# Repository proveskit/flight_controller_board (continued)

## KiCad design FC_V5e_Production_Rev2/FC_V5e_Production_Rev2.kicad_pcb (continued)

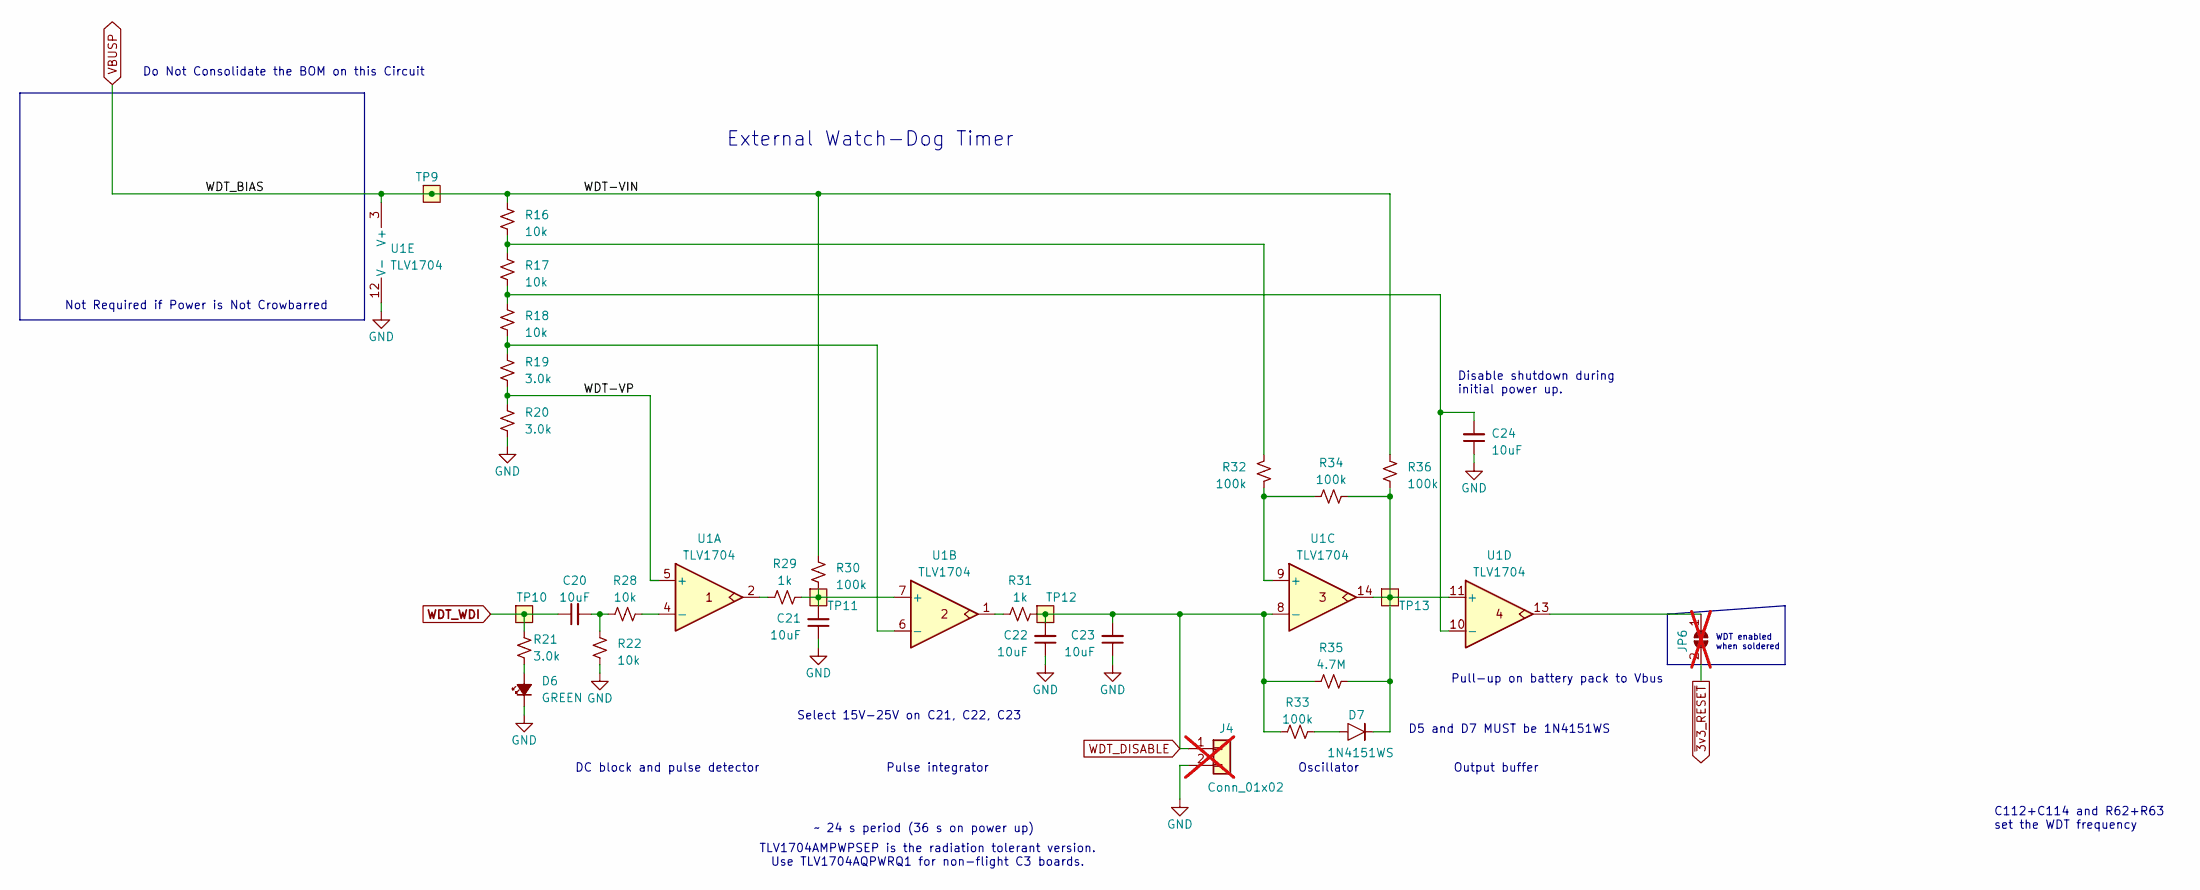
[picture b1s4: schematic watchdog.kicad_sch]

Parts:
C20, C24: 10uF; C_0603_1608Metric; MPN GRT188R61C106KE13D
C21, C22, C23: 10uF; C_0603_1608Metric; MPN CL10A106MA8NRNC
D6: GREEN; LED_0603_1608Metric; MPN 150060GS75000
D7: 1N4151WS; D_SOD-323; MPN 1N4151WS-E3-08
J4: Conn_01x02; PinHeader_1x02_P2.54mm_Vertical; not fitted
JP6: SolderJumper_2_Open; SolderJumper-2_P1.3mm_Open_RoundedPad1.0x1.5mm; not fitted
R16, R17, R18, R22, R28: 10k; R_0603_1608Metric; MPN RMCF0603FT10K0
R19, R20, R21: 3.0k; R_0603_1608Metric; MPN RMCF0603FT3K00
R29, R31: 1k; R_0603_1608Metric; MPN RMCF0603FT1K00
R30, R32, R33, R34, R36: 100k; R_0603_1608Metric; MPN RMCF0603FT100K
R35: 4.7M; R_0603_1608Metric; MPN RMCF0603FT4M70
TP9, TP10, TP11, TP12, TP13: TestPoint-MinTH; TestPoint-0.75mm-th
U1: TLV1704; TSSOP-14_4.4x5mm_P0.65mm; MPN TLV1704AQPWRQ1

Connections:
/Watchdog Circuit/WDT-VP: R19.2, R20.1, U1.5 (+)
GND: C21.1, C22.1, C23.1, C24.1, D6.1 (K), J4.2, R20.2, R22.2, U1.12 (V-); also elsewhere on the board
unnamed: C20.2, R22.1, R28.1
unnamed: D6.2 (A), R21.2
unnamed: D7.2, R33.1
unnamed: JP6.1 (A), U1.13
unnamed: R16.2, R17.1, R32.2
unnamed: R29.1, U1.2
unnamed: R31.1, U1.1
unnamed: R28.2, U1.4 (-)
unnamed: C21.2, R29.2, R30.2, TP11.1, U1.7 (+)
unnamed: R18.2, R19.1, U1.6 (-)
unnamed: R32.1, R34.1, U1.9 (+)
unnamed: D7.1, R34.2, R35.1, R36.1, TP13.1, U1.11 (+), U1.14
unnamed: C24.2, R17.2, R18.1, U1.10 (-)
VBUSP: R16.1, R30.1, R36.2, TP9.1, U1.3 (V+); also elsewhere on the board
WDT_DISABLE: C22.2, C23.2, J4.1, R31.2, R33.2, R35.2, TP12.1, U1.8 (-); also elsewhere on the board
WDT_WDI: C20.1, R21.1, TP10.1; also elsewhere on the board
~3v3_RESET: JP6.2 (B); also elsewhere on the board

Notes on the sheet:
Pull-up on battery pack to Vbus
Do Not Consolidate the BOM on this Circuit
Pulse integrator
Disable shutdown during initial power up.
~ 24 s period (36 s on power up)
D5 and D7 MUST be 1N4151WS
C112+C114 and R62+R63 set the WDT frequency
TLV1704AMPWPSEP is the radiation tolerant version. Use TLV1704AQPWRQ1 for non-flight C3 boards.
Select 15V-25V on C21, C22, C23
DC block and pulse detector
Oscillator
Output buffer
WDT enabled when soldered
External Watch-Dog Timer
Not Required if Power is Not Crowbarred

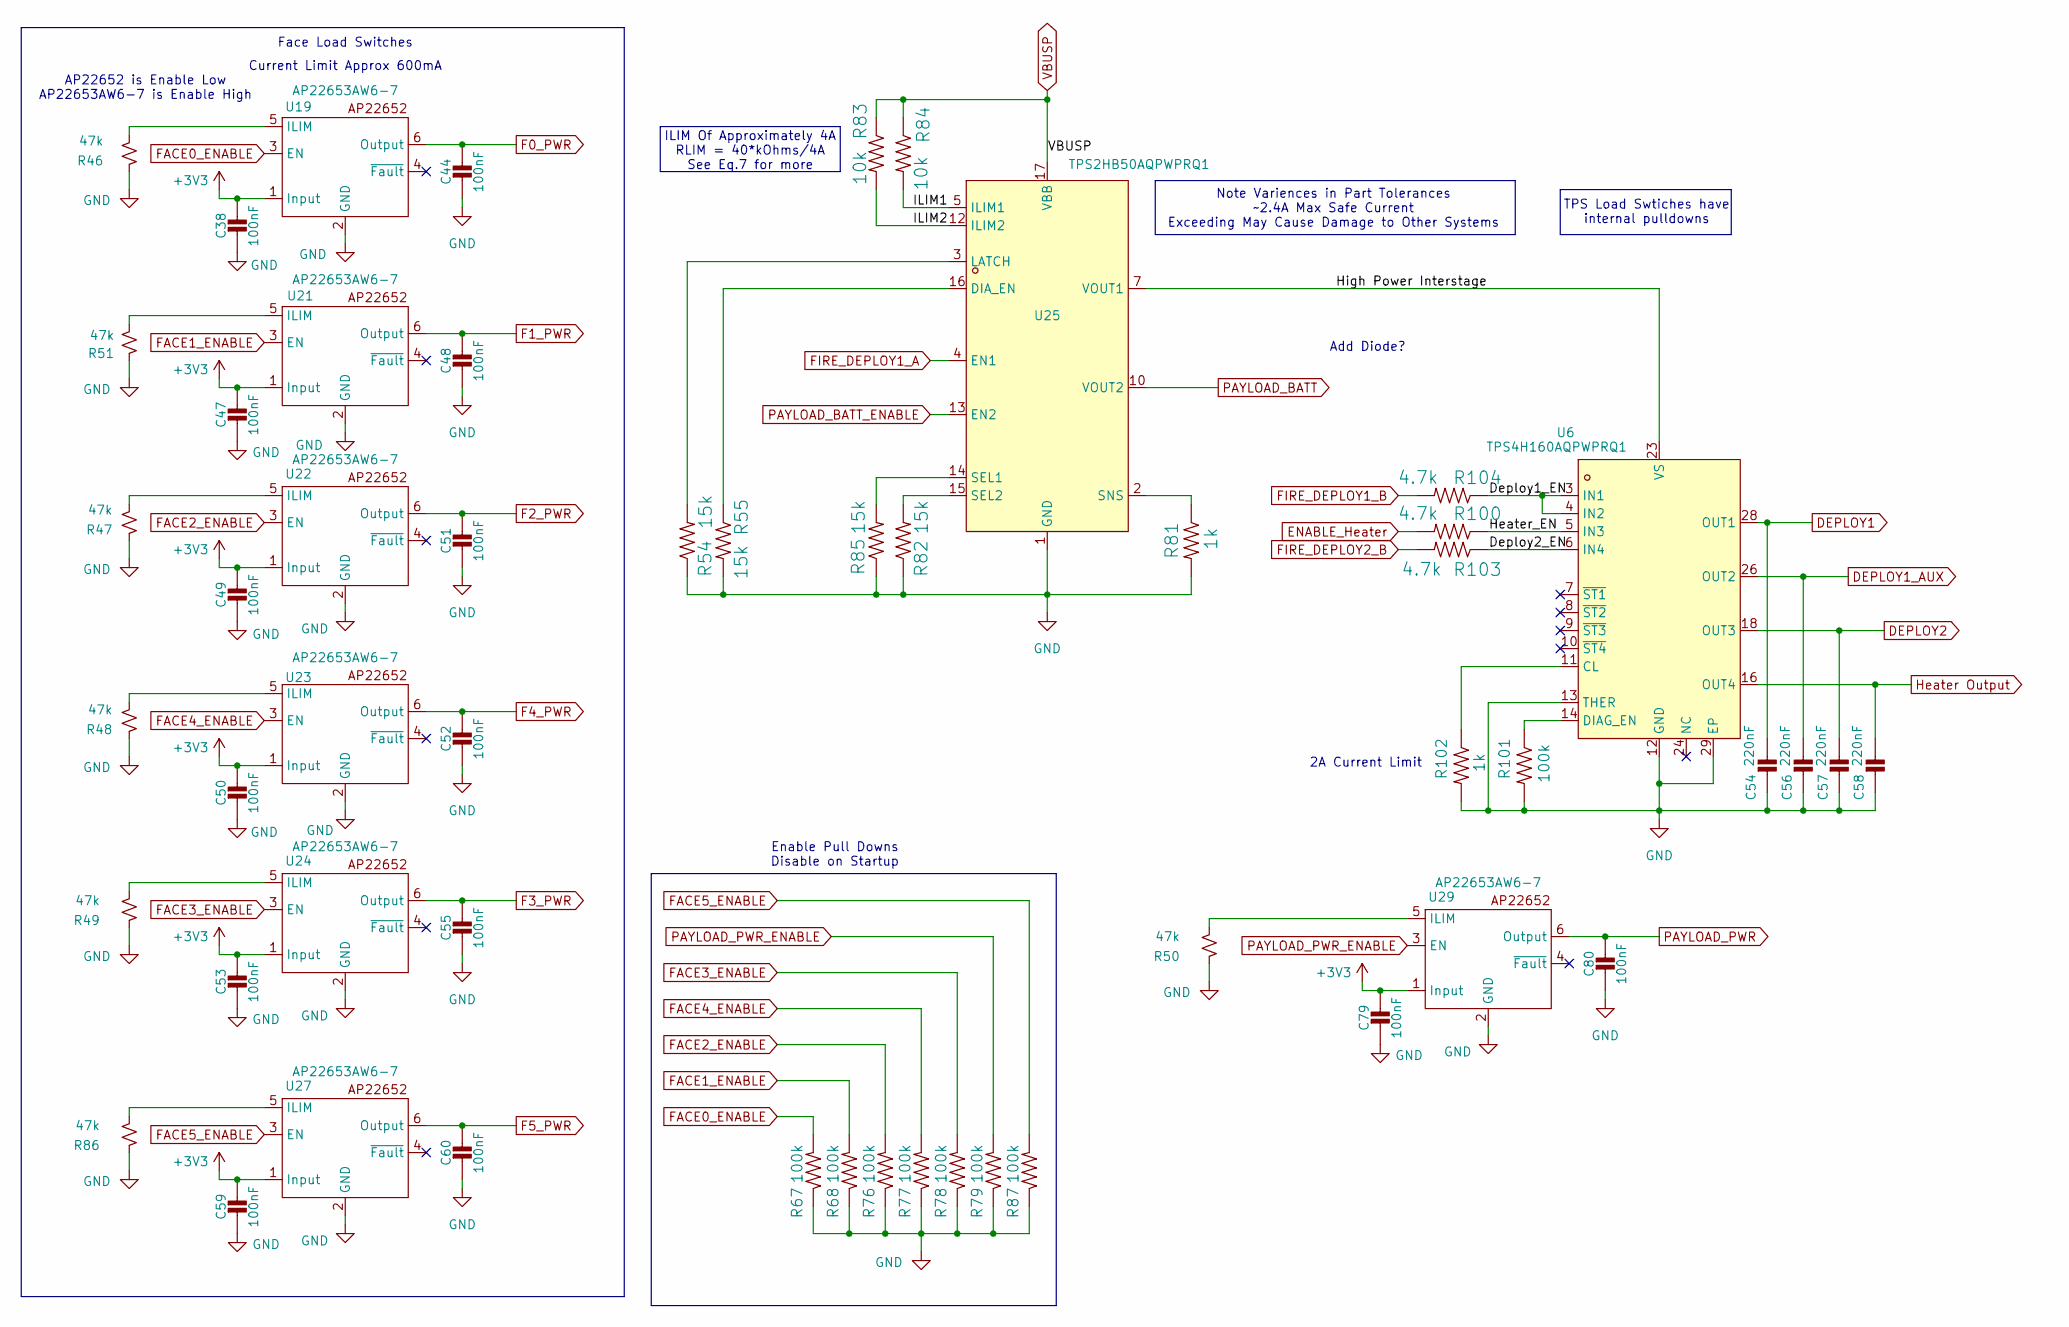
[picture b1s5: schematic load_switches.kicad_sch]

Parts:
C38, C44, C47, C48, C49, C50, C51, C52, C53, C55, C59, C60, C79, C80: 100nF; C_0402_1005Metric
C54, C56, C57, C58: 220nF; C_0402_1005Metric
R46, R47, R48, R49, R50, R51, R86: 47k; R_0603_1608Metric; MPN RMCF0603FT47K0
R54, R55, R82, R85: 15k; R_0603_1608Metric
R67, R68, R76, R77, R78, R79, R87, R101: 100k; R_0603_1608Metric
R81, R102: 1k; R_0603_1608Metric
R83, R84: 10k; R_0603_1608Metric
R100, R103, R104: 4.7k; R_0402_1005Metric
U6: TPS4H160AQPWPRQ1; HTSSOP-28_L9.7-W4.4-P0.65-LS6.4-BL-EP; LCSC Part C485918
U19, U21, U22, U23, U24, U27, U29: AP22653AW6-7; SOT26
U25: TPS2HB50AQPWPRQ1; HTSSOP-16_L5.0-W4.4-P0.65-LS6.4-BL-EP-2; LCSC Part C1857514

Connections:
+3V3: C38.1, C47.1, C49.1, C50.1, C53.1, C59.1, C79.1, U19.1 (Input), U21.1 (Input), U22.1 (Input), U23.1 (Input), U24.1 (Input), U27.1 (Input), U29.1 (Input); also elsewhere on the board
/Power Systems/Load Switches/Deploy1_EN: R104.1, U6.3 (IN1), U6.4 (IN2)
/Power Systems/Load Switches/Deploy2_EN: R103.1, U6.6 (IN4)
/Power Systems/Load Switches/Heater_EN: R100.1, U6.5 (IN3)
/Power Systems/Load Switches/High Power Interstage: U6.20 (VS), U6.21 (VS), U6.22 (VS), U6.23 (VS), U25.6 (VOUT1), U25.7 (VOUT1), U25.8 (VOUT1)
/Power Systems/Load Switches/ILIM1: R84.2, U25.5 (ILIM1)
/Power Systems/Load Switches/ILIM2: R83.2, U25.12 (ILIM2)
DEPLOY1: C54.1, U6.27 (OUT1), U6.28 (OUT1); also elsewhere on the board
DEPLOY1_AUX: C56.1, U6.25 (OUT2), U6.26 (OUT2); also elsewhere on the board
DEPLOY2: C57.1, U6.17 (OUT3), U6.18 (OUT3); also elsewhere on the board
ENABLE_Heater: R100.2; also elsewhere on the board
F0_PWR: C44.1, U19.6 (Output); also elsewhere on the board
F1_PWR: C48.1, U21.6 (Output); also elsewhere on the board
F2_PWR: C51.1, U22.6 (Output); also elsewhere on the board
F3_PWR: C55.1, U24.6 (Output); also elsewhere on the board
F4_PWR: C52.1, U23.6 (Output); also elsewhere on the board
F5_PWR: C60.1, U27.6 (Output); also elsewhere on the board
FACE0_ENABLE: R67.2, U19.3 (EN); also elsewhere on the board
FACE1_ENABLE: R68.2, U21.3 (EN); also elsewhere on the board
FACE2_ENABLE: R76.2, U22.3 (EN); also elsewhere on the board
FACE3_ENABLE: R78.2, U24.3 (EN); also elsewhere on the board
FACE4_ENABLE: R77.2, U23.3 (EN); also elsewhere on the board
FACE5_ENABLE: R87.2, U27.3 (EN); also elsewhere on the board
FIRE_DEPLOY1_A: U25.4 (EN1); also elsewhere on the board
FIRE_DEPLOY1_B: R104.2; also elsewhere on the board
FIRE_DEPLOY2_B: R103.2; also elsewhere on the board
GND: C38.2, C44.2, C47.2, C48.2, C49.2, C50.2, C51.2, C52.2, C53.2, C54.2, C55.2, C56.2, C57.2, C58.2, C59.2, C60.2, C79.2, C80.2, R46.1, R47.1, R48.1, R49.1, R50.1, R51.1, R54.1, R55.2, R67.1, R68.1, R76.1, R77.1, R78.1, R79.1, R81.2, R82.1, R85.1, R86.1, R87.1, R101.2, R102.2, U6.1 (GND), U6.12 (GND), U6.13 (THER), U6.29 (EP), U19.2 (GND), U21.2 (GND), U22.2 (GND), U23.2 (GND), U24.2 (GND), U25.1 (GND), U27.2 (GND), U29.2 (GND); also elsewhere on the board
Heater Output: C58.1, U6.15 (OUT4), U6.16 (OUT4); also elsewhere on the board
unnamed: R102.1, U6.11 (CL)
unnamed: R101.1, U6.14 (DIAG_EN)
unnamed: R46.2, U19.5 (ILIM)
unnamed: R51.2, U21.5 (ILIM)
unnamed: R47.2, U22.5 (ILIM)
unnamed: R48.2, U23.5 (ILIM)
unnamed: R49.2, U24.5 (ILIM)
unnamed: R55.1, U25.16 (DIA_EN)
unnamed: R54.2, U25.3 (LATCH)
unnamed: R85.2, U25.14 (SEL1)
unnamed: R82.2, U25.15 (SEL2)
unnamed: R81.1, U25.2 (SNS)
unnamed: R86.2, U27.5 (ILIM)
unnamed: R50.2, U29.5 (ILIM)
PAYLOAD_BATT: U25.9 (VOUT2), U25.10 (VOUT2), U25.11 (VOUT2); also elsewhere on the board
PAYLOAD_BATT_ENABLE: U25.13 (EN2); also elsewhere on the board
PAYLOAD_PWR: C80.1, U29.6 (Output); also elsewhere on the board
PAYLOAD_PWR_ENABLE: R79.2, U29.3 (EN); also elsewhere on the board
VBUSP: R83.1, R84.1, U25.17 (VBB); also elsewhere on the board

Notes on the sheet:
Current Limit Approx 600mA
ILIM Of Approximately 4A RLIM = 40*kOhms/4A See Eq.7 for more
TPS Load Swtiches have internal pulldowns
Add Diode?
Note Variences in Part Tolerances ~2.4A Max Safe Current Exceeding May Cause Damage to Other Systems
2A Current Limit
AP22652 is Enable Low AP22653AW6-7 is Enable High
Enable Pull Downs Disable on Startup
Face Load Switches

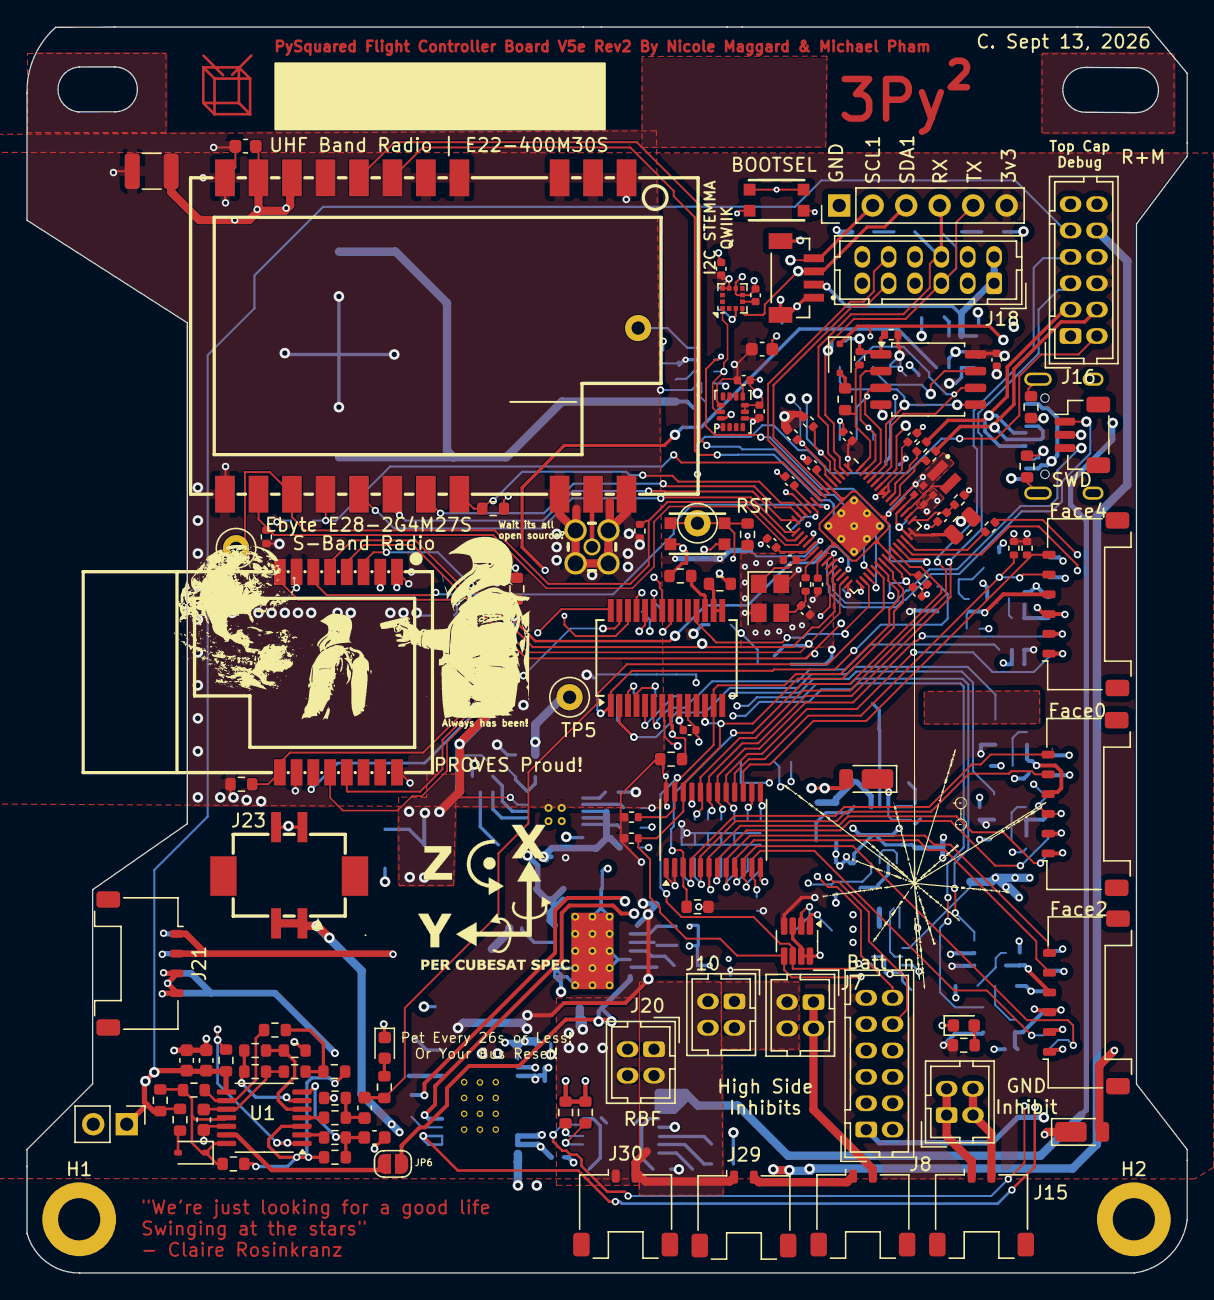
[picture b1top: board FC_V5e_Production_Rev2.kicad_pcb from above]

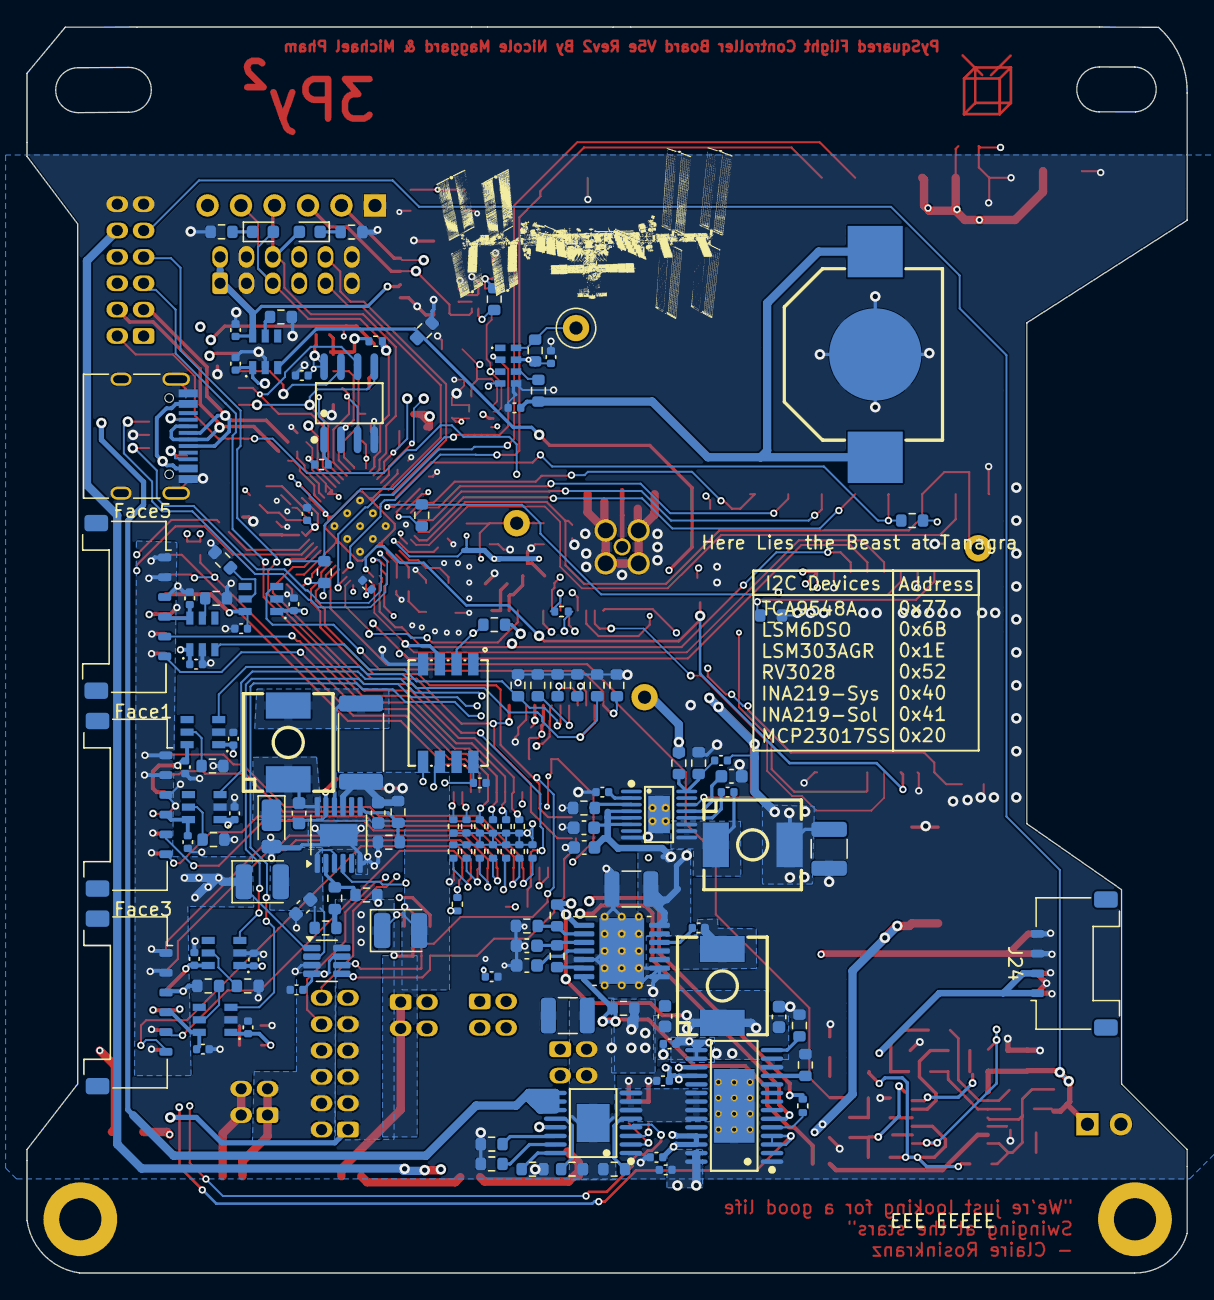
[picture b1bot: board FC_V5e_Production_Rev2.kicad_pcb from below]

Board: 4 copper layers, 88.0 x 94.5 mm, 256 parts (136 on the bottom side), 175 nets.

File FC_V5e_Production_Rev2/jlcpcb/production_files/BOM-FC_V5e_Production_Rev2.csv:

Comment,Designator,Footprint,LCSC,Quantity
0,R91,R_0402_1005Metric,C17168,1
0.1,R75,R_2512_6332Metric,C81248,1
100k,"R101,R30,R32,R33,R34,R36,R43,R65,R66,R67,R68,R76,R77,R78,R79,R80,R87,R92,R95,R96",R_0603_1608Metric,C25803,20
100nF,"C10,C18,C2,C26,C27,C28,C29,C30,C32,C34,C35,C38,C39,C44,C47,C48,C49,C5,C50,C51,C52,C53,C55,C59,C60,C67,C70,C71,C72,C73,C74,C76,C77,C78,C79,C80",C_0402_1005Metric,C1525,36
100uF,"C11,C19,C25",C_1210_3225Metric,C90143,3
10k,"R2,R37",R_0402_1005Metric,C25744,2
10k,"R1,R107,R11,R124,R13,R14,R15,R16,R17,R18,R22,R24,R28,R5,R52,R70,R83,R84,R90,R97",R_0603_1608Metric,C25804,20
10nF,C6,C_0402_1005Metric,C15195,1
10pF,C12,C_0402_1005Metric,C32949,1
10uF,C75,C_0805_2012Metric,C15850,1
10uF,"C1,C14,C20,C21,C22,C23,C24,C3,C40,C42,C43",C_0603_1608Metric,C19702,11
15k,"R54,R55,R82,R85",R_0603_1608Metric,C22809,4
15pF,"C63,C64",C_0402_1005Metric,C1548,2
1M,R63,R_0603_1608Metric,C22935,1
1N4151WS,D7,D_SOD-323,C17429783,1
1k,R93,R_0402_1005Metric,C11702,1
1k,"R10,R102,R29,R3,R31,R4,R64,R81",R_0603_1608Metric,C21190,8
1uF,"C37,C4,C41",C_0603_1608Metric,C15849,3
22,"R7,R8",R_0402_1005Metric,C25092,2
22.1k,R40,R_0603_1608Metric,C137768,1
220nF,"C31,C54,C56,C57,C58",C_0402_1005Metric,C16772,5
22uF,"C15,C16",C_0603_1608Metric,C59461,2
243k,R23,R_0603_1608Metric,C861248,1
2mOhm,"R108,R109",LED_1210_3225Metric,C92124,2
3.0k,"R19,R20,R21",R_0603_1608Metric,C4211,3
3.3nF,C36,C_0603_1608Metric,C1613,1
3.3u,L3,L_pol_2016,C42411119,1
33,R94,R_0402_1005Metric,C25105,1
4.7M,R35,R_0603_1608Metric,C18335,1
4.7k,"R100,R103,R104,R105,R106,R110,R111,R25,R39,R41,R44,R45,R53,R56,R57,R58,R59,R6,R60,R61,R62,R72,R73,R88,R89",R_0402_1005Metric,C25900,25
4.7uF,"C65,C66,C68,C69",C_0402_1005Metric_small_pads,C23733,4
412k,R74,R_0603_1608Metric,C23050,1
47k,"R46,R47,R48,R49,R50,R51,R86",R_0603_1608Metric,C25819,7
47uF,C8,C_1210_3225Metric,C84494,1
5.1k,"R26,R27",R_0603_1608Metric,C23186,2
52.3k,R42,R_0603_1608Metric,C227953,1
634k,R71,R_0603_1608Metric,C2999499,1
73.2k,R38,R_0603_1608Metric,C14890,1
94k,R69,R_0603_1608Metric,C861602,1
ABM8-272-T3,Y1,Crystal_SMD_3225-4Pin_3.2x2.5mm,C20625731,1
AP22653AW6-7,"U19,U21,U22,U23,U24,U27,U29",SOT26,C1511768,7
APS1604M-3SQR-SN_C18214056,U5,SOIC-8_L4.9-W3.9-P1.27-LS6.0-BL,C18214056,1
Aux Deploy 1,J23,CONN-SMD_4P-P2.00_DF11CZ-4DP-2V-27,C597838,1
BM04B-SRSS-TB(LF)(SN),J5,JST_BM04B-SRSS-TB(LF)(SN),C160390,1
Battery Input,J14,Hirose_DF11-12DP-2DSA_2x06_P2.00mm_Vertical,C506658,1
Conn_01x06,"J1,J11,J13,J2,J6,J9",Molex_Pico-Lock_504050-0691_1x06-1MP_P1.50mm_Horizontal,C563981,6
DEBUG,J16,Hirose_DF11-12DP-2DSA_2x06_P2.00mm_Vertical,C506658,1
DFLS130L,"D12,D13,D15",D_PowerDI-123,C110493,3
Deploy 2,J24,Molex_Pico-Lock_504050-0491_1x04-1MP_P1.50mm_Horizontal,C177235,1
E22-400M30S,U13,WIRELM-SMD_E22-400M30S,C411292,1
E28-2G4M27S,U30,WIRELM-SMD_E28-2G4M2XS,C411312,1
GREEN,D6,LED_0603_1608Metric,C12624,1
Heater Output,J21,Molex_Pico-Lock_504050-0491_1x04-1MP_P1.50mm_Horizontal,C177235,1
INA219AxDCN,"U16,U8",SOT-23-8,C87469,2
INHIBIT_P1,J7,Hirose_DF11-4DP-2DSA_2x02_P2.00mm_Vertical,C506665,1
INHIBIT_P2,J10,Hirose_DF11-4DP-2DSA_2x02_P2.00mm_Vertical,C506665,1
INHIBIT_S1_Picolock,J8,Molex_Pico-Lock_504050-0291_1x02-1MP_P1.50mm_Horizontal,C5119943,1
INHIBIT_S2_Picolock,J29,Molex_Pico-Lock_504050-0291_1x02-1MP_P1.50mm_Horizontal,C5119943,1
ISS_INHIBIT,J19,Hirose_DF11-4DP-2DSA_2x02_P2.00mm_Vertical,C506665,1
ISS_INHIBIT_Picolock,J15,Molex_Pico-Lock_504050-0291_1x02-1MP_P1.50mm_Horizontal,C5119943,1
KH-MMCX-Z,RF1,MMCX-TH_KH-MMCX-Z,C530664,1
KMR2,"SW1,SW2",BTN_KMR2_4.6X2.8,C72443,2
LED,"D1,D2,D3",LED_0603_1608Metric,C2290,3
LIS2MDL,U15,LGA-12_2x2mm_P0.5mm,C919695,1
LSM6DSOTR,U7,LGA-14_3x2.5mm_P0.5mm_LayoutBorder3x4y,C2655100,1
LT3652IMSE#PBF,IC6,MSOP-12-1EP_3x4mm_P0.65mm_EP1.65x2.85mm,C671115,1
LT8610ABEMSE#TRPBF,U12,MSOP-16_L4.0-W3.0-P0.50-LS4.9-BL-EP,C580306,1
MCP23017_SS,U9,SSOP-28_5.3x10.2mm_P0.65mm,C558584,1
MY-1220-03,BT1,BAT-SMD_MY-1220-03,C964818,1
NSR0320,D4,D_SOD-323F,C48192,1
Payload,J18,Hirose_DF11-12DP-2DSA_2x06_P2.00mm_Vertical,C506658,1
RBF_Inhibit,J20,Hirose_DF11-4DP-2DSA_2x02_P2.00mm_Vertical,C506665,1
RBF_Picolock,J30,Molex_Pico-Lock_504050-0291_1x02-1MP_P1.50mm_Horizontal,C5119943,1
RP2350_60QFN,U18,RP2350-QFN-60-1EP_7x7_P0.4mm_EP3.4x3.4mm_ThermalVias,C42411118,1
RV-3028-C7_32.768kHz_1ppm_TA_QA,IC3,RV3028C7,C3304278,1
SPM6530T-100M,L1,IND-SMD_L7.1-W6.5-P5.60,C112288,1
SPM6530T-3R3M-HZ,L4,IND-SMD_L7.1-W6.5,C404816,1
SPM6530T-4R7M-HZ,L5,IND-SMD_L7.1-W6.5-P5.60,C360729,1
SWD Port,J22,JST_SH_BM03B-SRSS-TB_1x03-1MP_P1.00mm_Vertical,C160389,1
TCA9548APWR,U3,TSSOP-24_4.4x7.8mm_P0.65mm,C130026,1
TLV1704,U1,TSSOP-14_4.4x5mm_P0.65mm,C181596,1
TPS2HB50AQPWPRQ1,U25,HTSSOP-16_L5.0-W4.4-P0.65-LS6.4-BL-EP-2,C1857514,1
TPS4H160AQPWPRQ1,U6,HTSSOP-28_L9.7-W4.4-P0.65-LS6.4-BL-EP,C485918,1
TPS54225PWPR,U10,HTSSOP-14-1EP_4.4x5mm_P0.65mm_EP3.4x5mm_Mask3x3.1mm_ThermalVias,C555460,1
USB_C_Receptacle_USB2.0_16P,J12,USB_C_Receptacle_HRO_TYPE-C-31-M-12,C165948,1
W25Q128JVS,U11,SOIC-8_5.3x5.3mm_P1.27mm,C97521,1
ZDSD02GLGEAG,U2,LGA-8_L8.0-W6.0-P1.27-TL-1,C2875853,1
RESET,TP2,TestPoint_Loop_D1.80mm_Drill1.0mm_Beaded,,1
Life Makes Lemonade,J3,PinHeader_1x06_P2.54mm_Vertical,,1
DNF,R9,R_0402_1005Metric,,1
RESET,TP6,TestPoint_Loop_D1.80mm_Drill1.0mm_Beaded,,1
RESET,TP8,TestPoint_Loop_D1.80mm_Drill1.0mm_Beaded,,1
SolderJumper_2_Open,JP6,SolderJumper-2_P1.3mm_Open_RoundedPad1.0x1.5mm,,1
TestPoint,TP5,TestPoint_Loop_D1.80mm_Drill1.0mm_Beaded,,1
Conn_01x02,J4,PinHeader_1x02_P2.54mm_Vertical,,1

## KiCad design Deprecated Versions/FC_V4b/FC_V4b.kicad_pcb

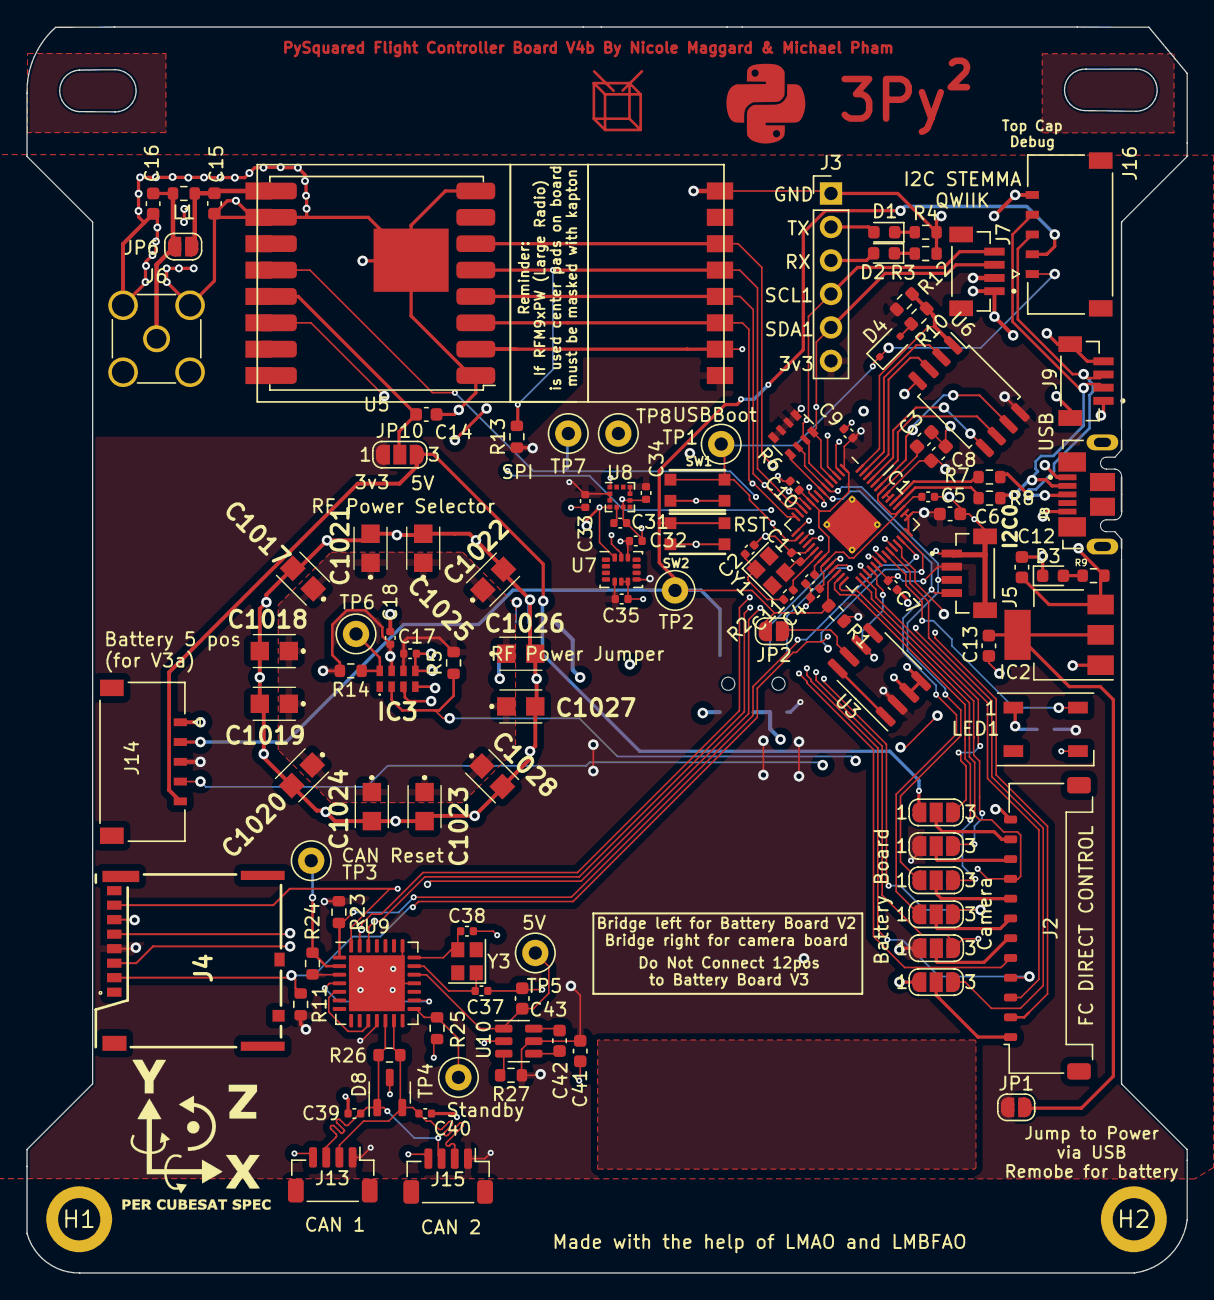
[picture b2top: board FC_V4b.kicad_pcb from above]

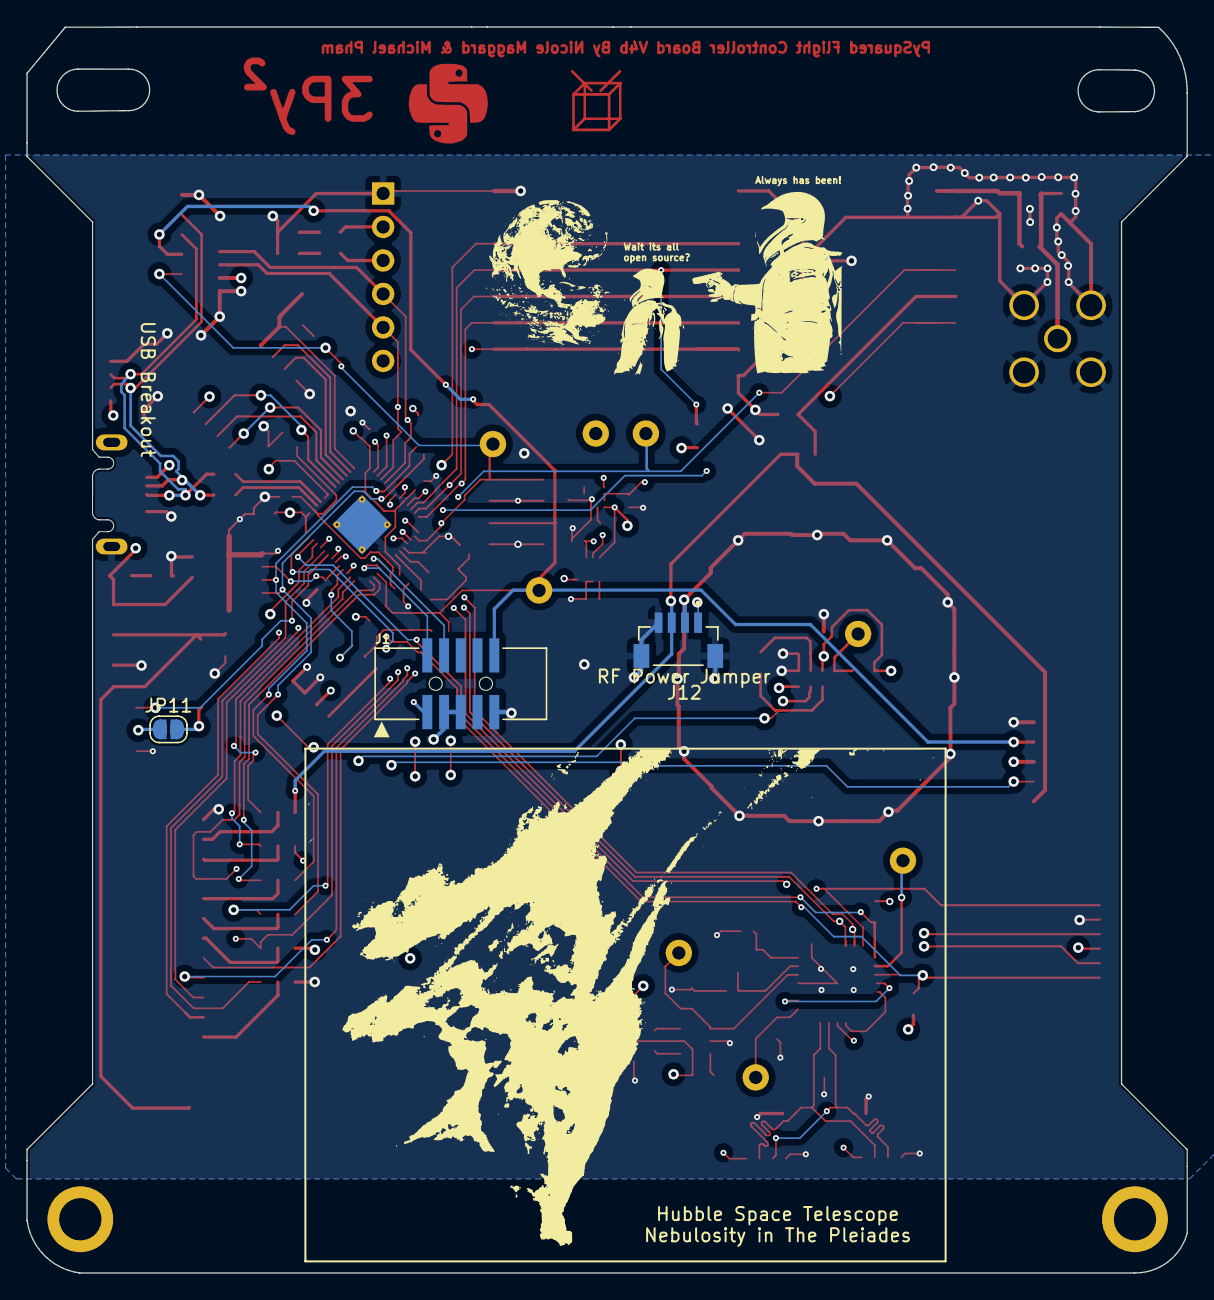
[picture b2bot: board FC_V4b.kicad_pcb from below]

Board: 4 copper layers, 88.0 x 94.5 mm, 118 parts (3 on the bottom side), 83 nets.

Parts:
C1, C2: 22pF; C_0402_1005Metric
C3, C6, C8: 1uF; C_0603_1608Metric
C4, C5, C7, C9, C10, C11, C17, C18, C32, C33, C34, C35: 100nf; C_0402_1005Metric
C12, C14: 10uF; C_0603_1608Metric
C13: 22uF; C_0603_1608Metric
C15, C16: DNI; C_0603_1608Metric
C31: 220nf; C_0402_1005Metric
C37, C38: 22pf; C_0402_1005Metric
C39, C40: 47pf; C_0402_1005Metric
C41, C43: 10uf; C_0603_1608Metric
C42: 1uf; C_0603_1608Metric
C1017, C1018, C1019, C1020, C1021, C1022, C1023, C1024, C1025, C1026, C1027, C1028: CPH3225A
D1, D2, D3: LED; LED_0603_1608Metric
D4: NSR0320; D_SOD-323F
D8: PESD1CAN; SOT-23-3
H1, H2: MountingHole
IC1: RP2040_QFN56; QFN-56-1EP_7x7mm_P0.4mm_EP3.2x3.2mm_ThermalVias
IC2: AZ1117CH-3.3TRG1; SOT-223
IC3: RV-3028-C7_32.768kHz_1ppm_TA_QC; RV3028C7
J1: Conn_ARM_JTAG_SWD_10; JTAG_2X05_1.27MM_BOX_NOCREAM
J2: FC to EPS Connector; Molex_Pico-Lock_504050-1291_1x12-1MP_P1.50mm_Horizontal
J3: Life Makes Lemonade; PinHeader_1x06_P2.54mm_Vertical
J4: Molex 503398-1892; 503398-1892-1
J5, J9, J12: BM04B-SRSS-TB(LF)(SN); JST_BM04B-SRSS-TB(LF)(SN)
J6: Conn_Coaxial; SMA_Amphenol_901-144_Vertical
J7: Breakout; JST_BM04B-SRSS-TB(LF)(SN)
J8: USB_B_Micro; MOLEX_105164-0001
J13, J15: Breakout; JST_SH_BM04B-SRSS-TB_1x04-1MP_P1.00mm_Vertical
J14: Battery; MOLEX_5040500591
J16: Debug; MOLEX_5040500591
JP1, JP2, JP6, JP11: SolderJumper_2_Open; SolderJumper-2_P1.3mm_Open_RoundedPad1.0x1.5mm
JP3, JP4, JP5, JP7, JP8, JP9, JP10: Jumper_3_Open; SolderJumper-3_P1.3mm_Open_RoundedPad1.0x1.5mm_NumberLabels
L1: DNI; R_0603_1608Metric
LED1: WS2812B_SK6812_1515; LED_WS2812B_PLCC4_5.0x5.0mm_P3.2mm
R1, R5, R9, R11, R12, R13, R14, R23, R24, R25, R27: 10k; R_0603_1608Metric
R2: 1k; R_0402_1005Metric
R3, R4, R10: 1k; R_0603_1608Metric
R6: 10k; R_Array_Convex_4x0603
R7, R8: 22; R_0603_1608Metric
R26: 120; R_0603_1608Metric
SW1, SW2: KMR2; BTN_KMR2_4.6X2.8
TP1: USBBOOT; TestPoint_Loop_D1.80mm_Drill1.0mm_Beaded
TP2, TP3, TP6, TP7, TP8: RESET; TestPoint_Loop_D1.80mm_Drill1.0mm_Beaded
TP4: Standby; TestPoint_Loop_D1.80mm_Drill1.0mm_Beaded
TP5: 5V; TestPoint_Loop_D1.80mm_Drill1.0mm_Beaded
U3: MAX706RESA; SO-8_3.9x4.9mm_P1.27mm
U4: RFM98PW
U5: RFM9xBreakout; HOPERF_RFM9XW_SMD
U6: W25Q128JV; SOIC-8_5.275x5.275mm_P1.27mm
U7: LSM6DSOTR; LGA-14_3x2.5mm_P0.5mm_LayoutBorder3x4y
U8: LSM303AGRTR; LGA-12_2x2mm_P0.5mm
U9: MCP25625-E/ML; QFN-28-1EP_6x6mm_P0.65mm_EP4.25x4.25mm
U10: AP3602AKTR-G1; SOT-23-6
Y1: 12MHZ; Crystal_SMD_2520-4Pin_2.5x2.0mm
Y3: 16MHZ 12 pf; Crystal_SMD_2520-4Pin_2.5x2.0mm

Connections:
1.2V: C3.1, C4.2, C5.2, IC1.23 (DVDD), IC1.45 (VREG_VOUT), IC1.50 (DVDD)
3.3V: C6.1, C7.1, C8.1, C9.1, C10.1, C11.1, C18.1, C32.1, C33.1, C34.1, C35.1, C41.2, IC1.1 (IOVDD), IC1.10 (IOVDD), IC1.22 (IOVDD), IC1.33 (IOVDD), IC1.42 (IOVDD), IC1.43 (ADC_IOVDD), IC1.44 (VREG_IOVDD), IC1.48 (USB_IOVDD), IC1.49 (IOVDD), IC3.7 (VDD), J1.1 (VTref), J3.6, J4.4 (VDD), J5.2, J7.2, J12.1, J13.1, J14.3, J15.1, JP1.1 (A), JP4.1 (A), JP5.1 (A), JP10.1 (A), JP11.1 (A), R1.1, R6.5 (R4.2), R6.6 (R3.2), R6.7 (R2.2), R6.8 (R1.2), R11.2, R12.1, R13.1, R14.2, R23.1, R24.1, R27.1, U3.2 (VCC), U4.9 (3.3V), U6.8 (VCC), U7.5 (VDDIO), U7.8 (VDD), U7.12 (CS), U8.2 (CS_XL), U8.3 (CS_MAG), U8.9 (VDD), U8.10 (VDD_IO), U9.3 (VDD@1), U9.11 (VIO), U10.5 (VIN)
+5V: C43.2, TP5.1, U9.19 (VDDA), U10.1 (VOUT)
/3v3 Spec: C13.1, IC2.2 (OUTPUT), IC2.4 (VOUT), JP1.2 (B)
/D+: IC1.47 (USB_D+), R7.1
/D-: IC1.46 (USB_D-), R8.1
/QSPI_CS: IC1.56 (~QSPI_CS), R10.1, R12.2, U6.1 (SSEL)
/QSPI_DATA[0]: IC1.53 (QSPI_SD0), U6.5 (MOSI)
/QSPI_DATA[1]: IC1.55 (QSPI_SD1), U6.2 (MISO)
/QSPI_DATA[2]: IC1.54 (QSPI_SD2), U6.3 (WP#/IO2)
/QSPI_DATA[3]: IC1.51 (QSPI_SD3), U6.7 (HOLD#/IO3)
/QSPI_SCK: IC1.52 (QSPI_SCLK), U6.6 (SCK)
BURN_RELAY_A / D5: IC1.18 (GPIO15), JP9.3 (B)
CANH: C40.2, D8.2, J13.2, J15.2, R26.2, U9.13 (CANH)
CANL: C39.1, D8.1, J13.3, J15.3, R26.1, U9.12 (CANL)
D0: IC1.41 (GPIO29/AD3), J14.4
D3: D4.1 (K), IC1.16 (GPIO13), J2.5, J16.1, SW1.A, SW1.A' (P1), TP1.1
D6: IC1.27 (GPIO16), JP8.3 (B)
D7: IC1.28 (GPIO17), J2.9
D8: IC1.29 (GPIO18), JP5.3 (B)
D9: IC1.30 (GPIO19), JP7.3 (B)
ENABLE_BURN / PC: IC1.8 (GPIO6), J2.3
ENAB_RF / D2: IC1.15 (GPIO12), J2.4
FC_RESET: IC1.26 (/RUN), J1.10 (~RESET), J14.2, J16.2, JP2.2 (B), R1.2, SW2.A, SW2.A' (P1), TP2.1
GND: C1.1, C2.1, C3.2, C4.1, C5.1, C6.2, C7.2, C8.2, C9.2, C10.2, C11.2, C12.2, C13.2, C14.1, C15.2, C16.2, C17.2, C18.2, C31.2, C32.2, C33.2, C34.2, C35.2, C37.2, C38.2, C39.2, C40.1, C41.1, C43.1, C1017.2 (-), C1018.2 (-), C1019.2 (-), C1020.2 (-), C1021.2 (-), C1022.2 (-), C1023.2 (-), C1024.2 (-), C1025.2 (-), C1026.2 (-), C1027.2 (-), C1028.2 (-), D3.1 (K), D8.3, IC1.19 (TESTEN), IC1.57 (GND), IC2.1 (ADJ/GND), IC3.5 (VSS), J1.3 (GND), J1.5 (GND), J1.9 (GNDDetect), J2.12, J3.1, J4.6 (VSS), J5.1, J5.S1 (SHIELD), J5.S2 (SHIELD), J6.2 (Ext), J7.1, J8.5 (GND), J8.SH1 (Shield), J9.4, J9.S1 (SHIELD), J9.S2 (SHIELD), J12.2, J12.4, J12.S1 (SHIELD), J12.S2 (SHIELD), J13.4, J14.1, J15.4, J16.5, JP3.1 (A), LED1.3 (GND), R3.2, R4.2, R25.1, SW1.B (S), SW1.B' (S1), SW2.B (S), SW2.B' (S1), U3.3 (GND), U3.4 (PFI), U4.2 (GND), U4.16 (GND), U4.17 (GND), U5.1 (GND), U5.8 (GND), U5.10 (GND), U6.4 (VSS), U7.6 (GND), U7.7 (GND), U8.6 (GND), U8.8 (GND), U9.18 (VSS@1), U9.22 (GND), U9.29 (GND@1), U10.2 (GND)
HS: IC1.37 (GPIO25), JP3.3 (B)
I2C_RESET / VS: IC1.9 (GPIO7), J2.2
NEOPIX: IC1.36 (GPIO24), LED1.4 (DI)
unnamed: C2.2, R2.2, Y1.1
unnamed: D1.1 (K), R4.1
unnamed: D2.1 (K), R3.1
unnamed: D3.2 (A), R9.2
unnamed: D4.2 (A), R10.2
unnamed: C1.2, IC1.20 (XIN), Y1.3 (2)
unnamed: IC1.21 (XOUT), R2.1
unnamed: IC3.8 (EVI), R14.1, TP6.1
unnamed: J2.1, JP3.2 (C)
unnamed: J2.6, JP4.2 (C)
unnamed: J2.7, JP9.2 (C)
unnamed: J2.8, JP8.2 (C)
unnamed: J2.10, JP5.2 (C)
unnamed: J2.11, JP7.2 (C)
unnamed: C16.1, J6.1 (In), JP6.1 (A), L1.2
unnamed: JP2.1 (A), U3.7 (~RESET)
unnamed: JP11.2 (B), LED1.1 (VDD)
unnamed: U3.1 (~MR), U3.8 (~WDO)
unnamed: C31.1, U8.5 (C1)
unnamed: C38.1, U9.21 (OSC1), Y3.3 (2)
unnamed: C37.1, U9.20 (OSC2), Y3.1
unnamed: R24.2, TP3.1, U9.2 (RESET)
unnamed: R25.2, TP4.1, U9.15 (STBY)
unnamed: R27.2, U10.3 (*SHDN)
unnamed: C42.2, U10.6 (C+)
unnamed: C42.1, U10.4 (C-)
RF1_ANT: C15.1, JP6.2 (B), L1.1, U4.1 (ANT), U5.9 (ANT)
RF1_IO0: IC1.35 (GPIO23), TP8.1, U4.6 (GPIO_0), U5.14 (DIO0)
RF1_IO4: IC1.34 (GPIO22), TP7.1, U4.4 (GPIO_4), U5.12 (BUSY)
RF1_RST: IC1.31 (GPIO20), U4.14 (RESET), U5.6 (~RESET)
RF_VCC: C14.2, JP10.2 (C), U4.5 (VCC), U5.13 (3V3)
RTC_INT: IC1.39 (GPIO27/AD1), IC3.2 (~INT), R5.1
RX: D2.2 (A), IC1.3 (GPIO1), J3.3
RXCAN: U9.5 (RXCAN), U9.10 (RXD)
SCL0: IC1.7 (GPIO5), J5.4, JP9.1 (A), R6.1 (R1.1)
SCL1: IC1.5 (GPIO3), IC3.3 (SCL), J3.4, J7.4, R6.3 (R3.1), U7.13 (SCL), U8.1 (SCL/SPC)
SDA0: IC1.6 (GPIO4), J5.3, JP8.1 (A), R6.2 (R2.1)
SDA1: IC1.4 (GPIO2), IC3.4 (SDA), J3.5, J7.3, R6.4 (R4.1), U7.14 (SDA), U8.4 (SDA/SDI/SDO)
SPI0_CS0: IC1.12 (GPIO9), R13.2, U4.13 (NSS), U5.5 (CS)
SPI0_CS1: IC1.38 (GPIO26/AD0), J4.2 (CD/DAT3), R11.1
SPI0_CS2: IC1.40 (GPIO28/AD2), R23.2, U9.1 (CS)
SPI0_MISO: IC1.11 (GPIO8), J4.7 (DAT0), U4.10 (MISO), U5.2 (MISO), U9.28 (SO)
SPI0_MOSI: IC1.14 (GPIO11), J4.3 (CMD), U4.11 (MOSI), U5.3 (MOSI), U9.27 (SI)
SPI0_SCK: IC1.13 (GPIO10), J4.5 (CLK), U4.12 (SCK), U5.4 (SCK), U9.26 (SCK)
SWCLK: IC1.24 (SWCLK), J1.4 (SWDCLK/TCK)
SWDIO: IC1.25 (SWDIO), J1.2 (SWDIO/TMS)
TX: D1.2 (A), IC1.2 (GPIO0), J3.2
TXCAN: U9.4 (TXCAN), U9.16 (TXD)
USB_D+: J8.3 (D+), J9.3, J16.3, R7.2
USB_D-: J8.2 (D-), J9.2, J16.4, R8.2
VBUS: C12.1, IC2.3 (INPUT), J8.1 (VBUS), J9.1, R9.1
VBUS_RESET / D4: IC1.17 (GPIO14), JP4.3 (B)
VCC_RF1: J12.3, J14.5, JP7.1 (A), JP10.3 (B)
V_BACKUP: C17.1, C1017.1 (+), C1018.1 (+), C1019.1 (+), C1020.1 (+), C1021.1 (+), C1022.1 (+), C1023.1 (+), C1024.1 (+), C1025.1 (+), C1026.1 (+), C1027.1 (+), C1028.1 (+), IC3.6 (VBACKUP), R5.2
WDT_WDI: IC1.32 (GPIO21), U3.6 (~WDI)
